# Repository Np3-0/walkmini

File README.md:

# Walk-Mini
A customizable, portable music player created for Hack Club: Fallout.

## About Walk-Mini
Music is one of the only genres that can connect people who believe in different topics, live in different areas, and who even speak different languages. However, it is becoming harder to listen to it, without shelling out 10 dollars a month, or buying a vinyl (which nobody will carry around). <br> People already carry around old IPods and other technology like this, so I wanted to make my own spin on it.

## Key Features
* Fully customizable theming
  - Users can print their own cases and choose between a wide range of themes for the firmware.
* Bluetooth, Headphone Jack, and Speaker support!
* 2.4 Inch TFT display with vibrant colors!
* Unlimited Song Storage!
  - Depends on SD size.
* And More!

## How to Use
1. Put in **4 AA Batteries**.
2. It should start up automatically!
   - I would recommend taking batteries out when not in use, in order to save power.
<br>
On the main page, there are six options (characterized with icons): Restart, Pause/Resume, Skip, Songs, Shuffle, and Settings.
<br>The settings page contains Customize, Bluetooth, and Contributions.

## How to Build
1. Buy all parts listed.
2. Print the case bottom, top, and battery cover (I would recommend either TPU or PLA).
3. Once the PCB arrives, solder all components onto it, following the PCB layout.
4. Connect a USB-C cable to the USB-header from your computer, and use the Arduino editor to flash the firmware onto the ESP.
5. Put the assembled PCB inside of the case, and enjoy!
6. Make sure you have songs loaded into the SD Card. 

## Photos
### **PCB**:<br> 
### **Zine:** <br> 
### **CAD: (Link [here](https://cad.onshape.com/documents/891581ea64ec99eaf423b0d6/w/ed4d009452ec0fea7080dfa2/e/6ade851cf838900c5ee38ccd?renderMode=0&uiState=6a30aacfb006c78147cf0bbc))** <br> 

##

## BOM
| Part Name      | Description | Quantity | Unit Price | Total Price | URL | Running Total |
| ----------- | ----------- | ----------- | ----------- | ----------- | ----------- | ----------- |
| ESP32-WROOM-32E-N4 | MCU | 1 | $3.22 | $3.22 | [AliExpress](https://www.aliexpress.us/item/3256806057158706.html?utparam-url=scene%3Asearch%7Cquery_from%3Apc_back_same_best%7Cx_object_id%3A1005006243473458%7C_p_origin_prod%3A&algo_pvid=df30c4ff-dec8-4a3b-af10-f2fe7d864fab&algo_exp_id=df30c4ff-dec8-4a3b-af10-f2fe7d864fab&pdp_ext_f=%7B%22order%22%3A%22237%22%2C%22fromPage%22%3A%22search%22%7D&pdp_npi=6%40dis%21USD%213.29%210.99%21%21%213.29%210.99%21%402103122117772588423246279e2c68%2112000052254647571%21sea%21US%210%21ABX%211%210%21n_tag%3A-29910%3Bd%3A73118c74%3Bm03_new_user%3A-29895%3BpisId%3A5000000203712600&gatewayAdapt=4itemAdapt) | $3.43
| CP2102-GMR | USB to UART | 1 | $0.80 | $0.80 | [AliBaba](https://www.alibaba.com/product-detail/New-and-Original-CP2102-GMR-Electronic_1601731751516.html?priceId=cb0ce5b769d94795981c469bdce9a953) | $4.28
| SD-6-B | SD Card Reader | 1 | $0.58[^1] | $0.58 | [Same Sky](https://www.sameskydevices.com/product/interconnect/connectors/memory-card-connectors/sd-card-connectors/sd-6-b?srsltid=AfmBOoril4IXa0zYMeqRdO9H5vuY9dfO0f5PHj1uIutQLSDhJAolr3nc) | $4.90
| 1825910-6 | 6mm Button | 6[^2] | $0.057 | 1.14 | [AliExpress](https://www.aliexpress.us/item/3256805658758223.html?algo_pvid=5b5d2596-e29a-46b4-bfae-5d09a7e446dd&algo_exp_id=5b5d2596-e29a-46b4-bfae-5d09a7e446dd-16&pdp_ext_f=%7B%22order%22%3A%223214%22%2C%22eval%22%3A%221%22%2C%22fromPage%22%3A%22search%22%7D&pdp_npi=6%40dis%21USD%211.09%210.99%21%21%211.09%210.99%21%402101e2b017785468262657316ef6b8%2112000034553364519%21sea%21US%210%21ABX%211%210%21n_tag%3A-29910%3Bd%3A1ae5c6f1%3Bm03_new_user%3A-29895%3BpisId%3A5000000203537363&curPageLogUid=a4N1OIlqDFoz&utparam-url=scene%3Asearch%7Cquery_from%3A%7Cx_object_id%3A1005005845072975%7C_p_origin_prod%3A) | $5.26
| PCM5102APWR | Audio Jack Controller | 1 | $1.00 | $1.00 | [AliBaba](https://www.alibaba.com/product-detail/PCM5102APWR-IC-Chip-20-TSSOP-Brand_1600511085959.html?priceId=ba42e2395af34fafaf9c4b6be956c1c8) | $6.33 
| MAX98357AETE+T | Speaker Controller | 1 | $0.10 | $0.10 | [AliBaba](https://www.alibaba.com/product-detail/New-and-Original-MAX98357AETE-T-Electronic_1601732000471.html?priceId=2ccbc724114a490fb1ee81e4e230e6b8) | $6.44
| SJ-3523-SMT-TR | Headphone Jack | 1 | $0.88 | $0.88 | [DigiKey](https://www.digikey.com/en/products/detail/same-sky-formerly-cui-devices/SJ-3523-SMT-TR/281297) | $7.38
| AI-4328-P-C120D-R | Speaker | 1 | $16.92 | $16.92 | [DigiKey](https://www.digikey.com/en/products/detail/pui-audio-inc/ai-4328-p-c120d-r/1738481) | $25.42
| 2477 | Battery Holder | 1 | $1.87 | $1.87 | [Digikey](https://www.digikey.com/en/products/detail/keystone-electronics/2477/303822) | $27.41
| MCP1826S-3302E/AB | LDO | 1 | $0.66 | $0.66 | [AliBaba](https://www.alibaba.com/product-detail/Electronic-Circuit-Components-MCP1826S-3302E-AB_1601731375638.html?priceId=8291b1507dca417ca7b029191e1e88de) | $28.11
| USB4085-GF-A | USB-C Connector | 1 | $0.04 | $0.04 | [AliBaba](https://www.alibaba.com/product-detail/Hainayu-BOM-capacitor-resistance-table-quotation_1601270438701.html?priceId=a70c80eafee34aba80d3bcf18a5baf0e) | $28.15
| 1N5819 | Schottky Diode | 1 | $0.01 | $0.01 | [AliBaba](https://www.alibaba.com/product-detail/Through-hole-Schottky-Diodes-1N5817-1N5818_1601557699434.html?selectedCarrierCode=SEMI_MANAGED_STANDARD%40%40STANDARD&priceId=6f243cc781264e41885941c826333b64) | $28.16
| SSK02-FPH-254-A14 | Display 14 Pin Connector | 1 | $0.54 | $0.54 | [DigiKey](https://www.digikey.com/en/products/detail/same-sky-formerly-cui-devices/SSK02-FPH-254-A14/28772145) | $28.74
| ILI9341 | 2.4 Inch TFT Display | 1 | $5.16 | $5.16 | [AliExpress](https://www.aliexpress.us/item/3256803732365701.html?algo_pvid=335efabf-7043-43e3-b1e5-88cb6faf5a31&algo_exp_id=335efabf-7043-43e3-b1e5-88cb6faf5a31-15&pdp_ext_f=%7B%22order%22%3A%22208%22%2C%22eval%22%3A%221%22%2C%22fromPage%22%3A%22search%22%7D&pdp_npi=6%40dis%21USD%214.45%211.78%21%21%214.45%211.78%21%402103128917785486140741950e4710%2112000056542062912%21sea%21US%210%21ABX%211%210%21n_tag%3A-29910%3Bd%3A46ae3b9e%3Bm03_new_user%3A-29895%3BpisId%3A5000000204886261&curPageLogUid=W4D3fCRCIHOw&utparam-url=scene%3Asearch%7Cquery_from%3A%7Cx_object_id%3A1005003918680453%7C_p_origin_prod%3A) | $34.24
| PCB | JLCPCB for project | 5 | $1.64 | $8.20 | [JLCPCB](https://jlcpcb.com/) | $42.98
| ABS07-32.768KHZ-T | 32.768 Khz Crsytal | 1 | $0.61 | $0.61 | [Digikey](https://www.digikey.com/en/products/detail/abracon-llc/ABS07-32-768KHZ-T/1236858) | $43.63
| MBA02040C3003FC100 | 300K Ohm Resistor | 1 | $0.66 | $0.66 | [Digikey](https://www.digikey.com/en/products/detail/vishay-beyschlag-draloric-bc-components/MBA02040C3003FC100/7350347) | $44.33
| MBA02040C1002FRP00 | 10K Ohm Resistor | 10 | $0.095 | $0.95 | [Digikey](https://www.digikey.com/en/products/detail/vishay-beyschlag-draloric-bc-components/MBA02040C1002FRP00/336349) | $45.34
| MBA02040Z0000ZCT00 | 0 Ohm Resistor | 2 | $0.14 | $0.28 | [Digikey](https://www.digikey.com/en/products/detail/vishay-beyschlag-draloric-bc-components/MBA02040Z0000ZCT00/5066485) | $45.64
| MBA02040C5104FC100 | 5M Ohm Resistor | 1 | $0.39 | $0.39 | [Digikey](https://www.digikey.com/en/products/detail/vishay-beyschlag-draloric-bc-components/MBA02040C5104FC100/5059352?s=N4IgjCBcoCwGxVAYygMwIYBsDOBTANCAPZQDaIA7BQJwQC6hADgC5QgDKzATgJYB2AcxABfQgCYADAA4ArIhApIGHAWJkQMgHRgABAFkA8gAsAtthAMQLNgFU%2BPZgdR7c6bAFcuuEYQC0Y%2BUVud1USSHI5OmFREADwkC9sHmxmIi5zKKA) | $46.06
| MBA02040C4707JC100 | 470 Ohm Resistor | 2 | $0.11 | $0.22 | [Digikey](https://www.digikey.com/en/products/detail/vishay-beyschlag-draloric-bc-components/MBA02040C4700FRP00/333739) | $46.29
| MBA02040C5101FRP00 | 5.1K Ohm Resistor | 2 | $0.11 | $0.22 | [Digikey](https://www.digikey.com/en/products/detail/vishay-beyschlag-draloric-bc-components/MBA02040C5101FRP00/333758) | $46.52
| MBA02040C2209FCT00 | 22 Ohm Resistor | 2 | $0.21 | $0.42 | [Digikey](https://www.digikey.com/en/products/detail/vishay-beyschlag-draloric-bc-components/MBA02040C2209FCT00/5062426) | $46.97
| FK14X5R0J226MR020 | 22 µF Capacitor | 2 | $0.50 | $1.00 | [Digikey](https://www.digikey.com/en/products/detail/tdk/FK14X5R0J226MR020/2815215) | $48.04
| FK14X7R2A104KN020 | 0.1 µF Capacitor | 10 | $0.253 | $2.53 | [Digikey](https://www.digikey.com/en/products/detail/tdk/FK14X7R2A104KN020/2815243) | $50.74
| FG18C0G1H120JNT06 | 12pF Capacitor | 2 | $0.22 | $0.44 | [Digikey](https://www.digikey.com/en/products/detail/tdk/FG18C0G1H120JNT06/5802787) | $51.21
| FG18X7R1A225KRT06 | 2.2 µF Capacitor | 4 | $0.32 | $1.28 | [Digikey](https://www.digikey.com/en/products/detail/tdk/FG18X7R1A225KRT06/5802874) | $52.57
| FK18X5R0J105KN020 | 1 µF Capacitor | 2 | $0.28 | $0.56 | [Digikey](https://www.digikey.com/en/products/detail/tdk/FK18X5R0J105KN020/2815325) | $53.17
| FK18X5R1A475KR020 | 4.7 µF Capacitor | 1 | $0.34 | $0.34 | [Digikey](https://www.digikey.com/en/products/detail/tdk/FK18X5R1A475KR020/2815334) | $53.53
| ECE-A1EKA100I | 10 µF Polarized Capacitor | 5 | $0.26 | $1.30 | [Digikey](https://www.digikey.com/en/products/detail/panasonic-industry/ECE-A1EKA100I/2689086) | $54.92

**Enjoy!**
---
Made with love by Np3 (nate), 17, NJ

[^1]: Price is assumed for one SD-reader. For multiple, go [here:](https://www.alibaba.com/product-detail/Brand-New-Original-CONN-SD-CARD_1601485307544.html?priceId=8b2470e5a66946c49b35714d15eefd60)
[^2]: Button comes in package of 20.

# License
Shield: [![CC BY-NC-SA 4.0][cc-by-nc-sa-shield]][cc-by-nc-sa]

This work is licensed under a
[Creative Commons Attribution-NonCommercial-ShareAlike 4.0 International License][cc-by-nc-sa].

[![CC BY-NC-SA 4.0][cc-by-nc-sa-image]][cc-by-nc-sa]

[cc-by-nc-sa]: http://creativecommons.org/licenses/by-nc-sa/4.0/
[cc-by-nc-sa-image]: https://licensebuttons.net/l/by-nc-sa/4.0/88x31.png
[cc-by-nc-sa-shield]: https://img.shields.io/badge/License-CC%20BY--NC--SA%204.0-lightgrey.svg

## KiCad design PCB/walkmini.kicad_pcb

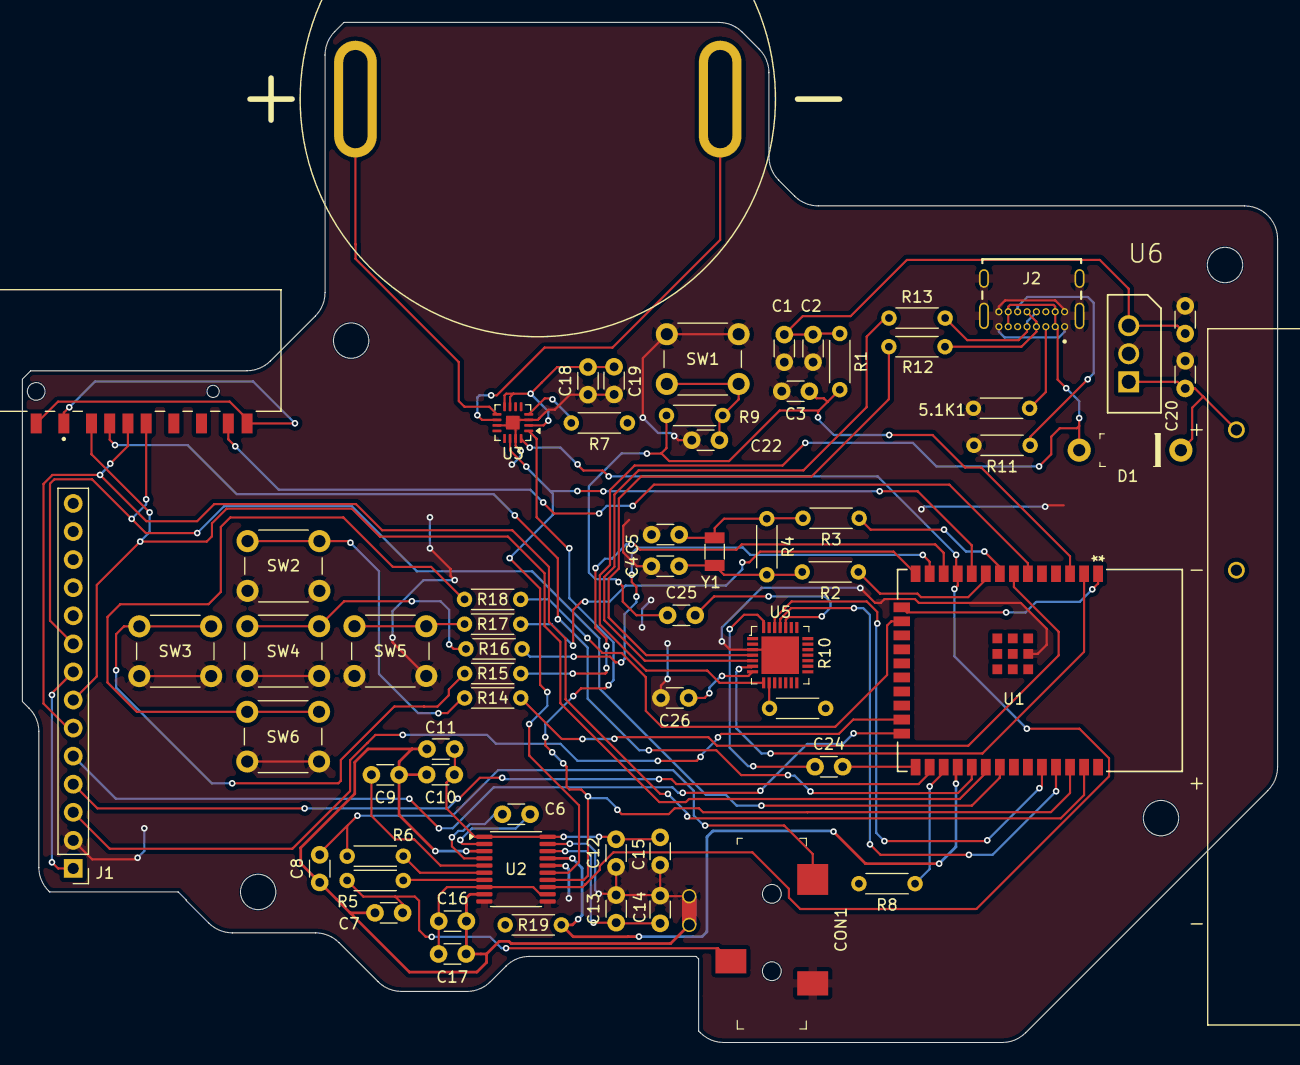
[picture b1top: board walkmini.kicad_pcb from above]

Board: 2 copper layers, 113.6 x 92.3 mm, 64 parts (0 on the bottom side), 53 nets.

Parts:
5.1K1: 300K; R_Axial_DIN0204_L3.6mm_D1.6mm_P5.08mm_Horizontal
BT1: 6V; BAT_2477
C1: 22uF; C_Disc_D3.0mm_W1.6mm_P2.50mm
C2, C10, C12, C13, C16, C18, C22: 0.1uF; C_Disc_D3.0mm_W1.6mm_P2.50mm
C3, C24, C25: 100nF; C_Disc_D3.0mm_W1.6mm_P2.50mm
C4, C5: 12pF; C_Disc_D3.0mm_W1.6mm_P2.50mm
C6, C7, C8, C9: 2.2uF; C_Disc_D3.0mm_W1.6mm_P2.50mm
C11, C14, C15, C17, C19: 10uF; C_Disc_D3.0mm_W1.6mm_P2.50mm
C20, C21: 1 uF; C_Disc_D3.0mm_W1.6mm_P2.50mm
C26: 4.7uF; C_Disc_D3.0mm_W1.6mm_P2.50mm
CON1: SJ-3523-SMT-TR; Switch_Slide_11.6x4mm_SJ-3523-SMT
D1: 1N5819; DO-41
J1: Conn_01x14; PinHeader_1x14_P2.54mm_Vertical
J2: USB4085-GF-A_REVB; GCT_USB4085-GF-A_REVB
LS1: Speaker; XDCR_AI-4328-P-C120D-R
R1, R8, R9, R10, R14, R15, R16, R17, R18, R19: 10K; R_Axial_DIN0204_L3.6mm_D1.6mm_P5.08mm_Horizontal
R2, R3: 0 NC; R_Axial_DIN0204_L3.6mm_D1.6mm_P5.08mm_Horizontal
R4: 5; R_Axial_DIN0204_L3.6mm_D1.6mm_P5.08mm_Horizontal
R5, R6: 470; R_Axial_DIN0204_L3.6mm_D1.6mm_P5.08mm_Horizontal
R7: 300K; R_Axial_DIN0204_L3.6mm_D1.6mm_P5.08mm_Horizontal
R11: 5.1K; R_Axial_DIN0204_L3.6mm_D1.6mm_P5.08mm_Horizontal
R12, R13: 22; R_Axial_DIN0204_L3.6mm_D1.6mm_P5.08mm_Horizontal
SD_R1: CUI_SD-6-B
SW1, SW2, SW3, SW4, SW5, SW6: SW_Push; SW_PUSH_6mm
U1: ESP32-WROOM-32E-N4; ESP32­WROOM­32E_EXP
U2: PCM5102A; TSSOP-20_4.4x6.5mm_P0.65mm
U3: MAX98357A; TQFN-16-1EP_3x3mm_P0.5mm_EP1.23x1.23mm
U5: CP2102-GMR_NRND; VFQFN-28-1EP_5x5mm
U6: MCP1826S; TO254P482X1024X3124-3P
Y1: 32.768Khz; Crystal_SMD_3215-2Pin_3.2x1.5mm

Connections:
+3V3: C1.1, C2.1, C10.1, C11.1, C12.2, C15.1, C16.1, C17.1, C18.2, C19.2, C21.1, C26.1, J1.1, J1.8, R1.1, R7.1, R8.2, R10.2, R14.1, R15.1, R16.1, R17.1, R18.1, R19.1, SD_R1.P1, SD_R1.P8, SD_R1.P9, U1.2 (3V3), U1.7 (IO35), U1.12 (IO27), U1.13 (IO14), U1.14 (IO12), U1.16 (IO13), U2.1 (CPVDD), U2.8 (AVDD), U2.12 (SCK), U2.20 (DVDD), U3.2 (GAIN_SLOT), U3.7 (VDD), U3.8 (VDD), U5.6 (VDD), U5.7 (REGIN), U6.3 (VO)
GND: 5.1K1.1, C1.2, C2.2, C3.2, C4.1, C5.2, C12.1, C13.2, C14.2, C15.2, C18.1, C19.1, C20.2, C21.2, C22.1, C26.2, CON1.1 (S), J1.2, J2.A1 (GND), J2.A12 (GND__1), J2.B1 (GND__2), J2.B12 (GND__3), J2.S1 (SHELL), J2.S2 (SHELL__1), J2.S3 (SHELL__2), J2.S4 (SHELL__3), R11.2, SW1.2, SW2.1, SW3.1, SW4.1, SW5.1, SW6.1, U1.47 (GND), U2.10 (DEMP), U2.11 (FLT), U2.16 (FMT), U2.19 (DGND), U3.3 (GND), U3.11 (GND), U3.15 (GND), U3.17 (PAD), U5.3 (GND), U5.29 (GND_PAD), U6.2 (GND)
GNDA: C7.1, C8.1, C9.1, C10.2, C11.2, C16.2, C17.2, U2.3 (CPGND), U2.9 (AGND)
unnamed: BT1.P, C20.1, D1.K, U6.1 (VI)
unnamed: C4.2, R2.2, R4.2, Y1.2
unnamed: C5.1, R3.2, R4.1, Y1.1
unnamed: C22.2, R9.1, SW1.1
unnamed: C7.2, CON1.3 (R), R5.1
unnamed: C8.2, CON1.2 (T), R6.2
unnamed: J1.3, U1.23 (IO15)
unnamed: J1.4, U1.26 (IO4)
unnamed: J1.5, U1.24 (IO2)
unnamed: J1.6, SD_R1.P3, U1.37 (IO23)
unnamed: J1.7, SD_R1.P2, U1.30 (IO18)
unnamed: J1.9, SD_R1.P4, U1.31 (IO19)
unnamed: 5.1K1.2, J2.A5 (CC1)
unnamed: J2.B5 (CC2), R11.1
unnamed: J2.A7 (DN1), J2.B7 (DN2), R13.2
unnamed: J2.A6 (DP1), J2.B6 (DP2), R12.2
unnamed: D1.A, J2.A4 (VBUS), J2.A9 (VBUS__1), J2.B4 (VBUS__2), J2.B9 (VBUS__3), U5.8 (VBUS)
unnamed: R14.2, SW2.2
unnamed: R15.2, SW3.2
unnamed: R16.2, SW4.2
unnamed: R17.2, SW5.2
unnamed: R18.2, SW6.2
unnamed: SD_R1.P7, U1.6 (IO34)
unnamed: SD_R1.CD, U1.29 (IO5)
unnamed: C3.1, C25.1, R1.2, R9.2, U1.3 (EN)
unnamed: U1.1 (GND), U1.15 (GND)
unnamed: C24.2, U1.25 (IO0)
unnamed: R8.1, U1.27 (IO16)
unnamed: U1.36 (IO22), U2.14 (DIN), U3.1 (DIN)
unnamed: U1.10 (IO25), U2.15 (LRCK), U3.14 (LRCLK)
unnamed: U1.11 (IO26), U2.13 (BCK), U3.16 (BCLK)
unnamed: R3.1, U1.8 (IO32)
unnamed: R2.1, U1.9 (IO33)
unnamed: U1.34 (RXD0), U5.26 (TXD)
unnamed: U1.35 (TXD0), U5.25 (RXD)
unnamed: C6.1, U2.4 (CAPM)
unnamed: C6.2, U2.2 (CAPP)
unnamed: C13.1, C14.1, U2.18 (LDOO)
unnamed: R6.1, U2.6 (OUTL)
unnamed: R5.2, U2.7 (OUTR)
unnamed: C9.2, U2.5 (VNEG)
unnamed: R19.2, U1.28 (IO17), U2.17 (XSMT)
unnamed: LS1.N, U3.10 (OUTN)
unnamed: LS1.P, U3.9 (OUTP)
unnamed: R7.2, U3.4 (~SD_MODE)
unnamed: R12.1, U5.4 (D+)
unnamed: R13.1, U5.5 (D-)
unnamed: C24.1, U5.28 (DTR)
unnamed: R10.1, U5.9 (RST)
unnamed: C25.2, U5.24 (RTS)

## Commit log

2026-05-11 start readme
2026-05-12 added to BOM
2026-05-12 BOM done
2026-05-14 spelling fix
2026-05-16 Add license section and badge to README
2026-05-16 added license
2026-05-16 upload BOM
2026-05-16 update readme BOM
2026-05-16 update BOM
2026-05-19 update BOM again
    Updated BOM.csv to reflect new part names and prices.
2026-05-19 added links
2026-05-19 fix BOM
    Updated component list with new parts and prices.
2026-05-19 fixing bom yet again
2026-05-24 add gerbers
2026-05-24 added pcb photo
2026-05-24 added code
2026-05-31 update BOM prices
2026-05-31 changed gerbers
2026-06-01 updating gerbers
2026-06-03 swapping license 1
2026-06-03 swapped license 2
2026-06-03 added zine
2026-06-16 added CAD
2026-06-16 fixed cad
2026-06-16 upload zine pdf
2026-06-16 remove redundant info
    Removed CC BY-NC-ND 4.0 shield from the README.
2026-06-16 added other pcb files
2026-06-16 added instructions
